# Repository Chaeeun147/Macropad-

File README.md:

This is my  number macropad called Bento Buttons!!

It has 9 buttons arranged in a standard 3-by-3 MX switch layout, with each button assigned a number. It also has custom keycaps I made.

I decided to make this because I saw my friend have one and thought it was very nice. But I never found a justifiable reason to buy it for myself. So I decided, instead of buying one with money, I should make it myself! Therefore, I made this project!

Case Onspae Project Link:
https://cad.onshape.com/documents/b9ad67c2619a28230095964c/w/e97b6c9aa4d60c46a3c97c60/e/4f1c892a648408b650cc743c?renderMode=0&uiState=69ecc582b69343973a4b0322

Keycap Onshape Project Link:
https://cad.onshape.com/documents/011ac684179c40686769cfd5/w/52282f15d2c1c6dc678585c8/e/da4142377097f970f64a90cc?renderMode=0&uiState=69ecc4f1b2576af614260f4a

3D Model:

PCB 3D Viewer:

PCB:

Schematic:

Case:

Keycaps:

BOM:
| Part Name | Quantity | Description | Cost | Link  |
| --------- | -------- | ----------- | ---- | - |
| Xiao RP 2040 | 1 | PCB | $3.59 |https://www.aliexpress.com/item/1005003908237026.html?spm=a2g0o.cart.0.0.6df938dabXCDew&mp=1&pdp_npi=6%40dis%21CAD%21CAD+11.73%21CAD+4.93%21%21CAD+4.75%21%21%21%40210328df17740487064442830e3672%2112000056511616306%21ct%21CA%217451194651%21%216%210%21) |
| Cherry MX Switch | 10 | Input | $2.60 | https://www.aliexpress.com/item/1005008811335051.html?spm=a2g0o.cart.0.0.6df938dabXCDew&mp=1&pdp_npi=6%40dis%21CAD%21CAD+52.73%21CAD+45.79%21%21CAD+44.15%21%21%21%40210328df17740487064442830e3672%2112000046764301536%21ct%21CA%217451194651%21%211%210%21 |
| Custom PCB | 5 | PCB | $2.00 | https://jlcpcb.com/ |
| 3D Printing | 1 | 3D Printing | $0.00 |  |

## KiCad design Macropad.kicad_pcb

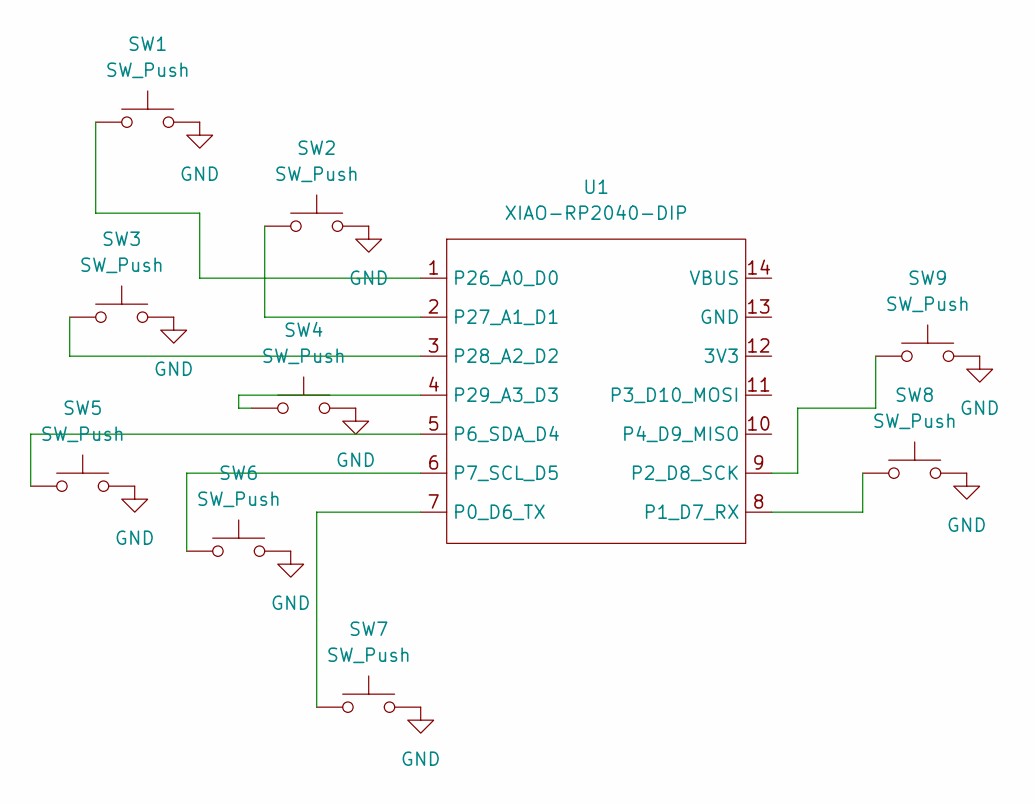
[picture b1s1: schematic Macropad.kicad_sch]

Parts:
SW1, SW2, SW3, SW4, SW5, SW6, SW7, SW8, SW9: SW_Push; SW_Cherry_MX_1.00u_PCB
U1: XIAO-RP2040-DIP

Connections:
GND: SW1.2, SW2.2, SW3.2, SW4.2, SW5.2, SW6.2, SW7.2, SW8.2, SW9.2
unnamed: SW7.1, U1.7 (P0_D6_TX)
unnamed: SW8.1, U1.8 (P1_D7_RX)
unnamed: SW9.1, U1.9 (P2_D8_SCK)
unnamed: SW5.1, U1.5 (P6_SDA_D4)
unnamed: SW6.1, U1.6 (P7_SCL_D5)
unnamed: SW1.1, U1.1 (P26_A0_D0)
unnamed: SW2.1, U1.2 (P27_A1_D1)
unnamed: SW3.1, U1.3 (P28_A2_D2)
unnamed: SW4.1, U1.4 (P29_A3_D3)

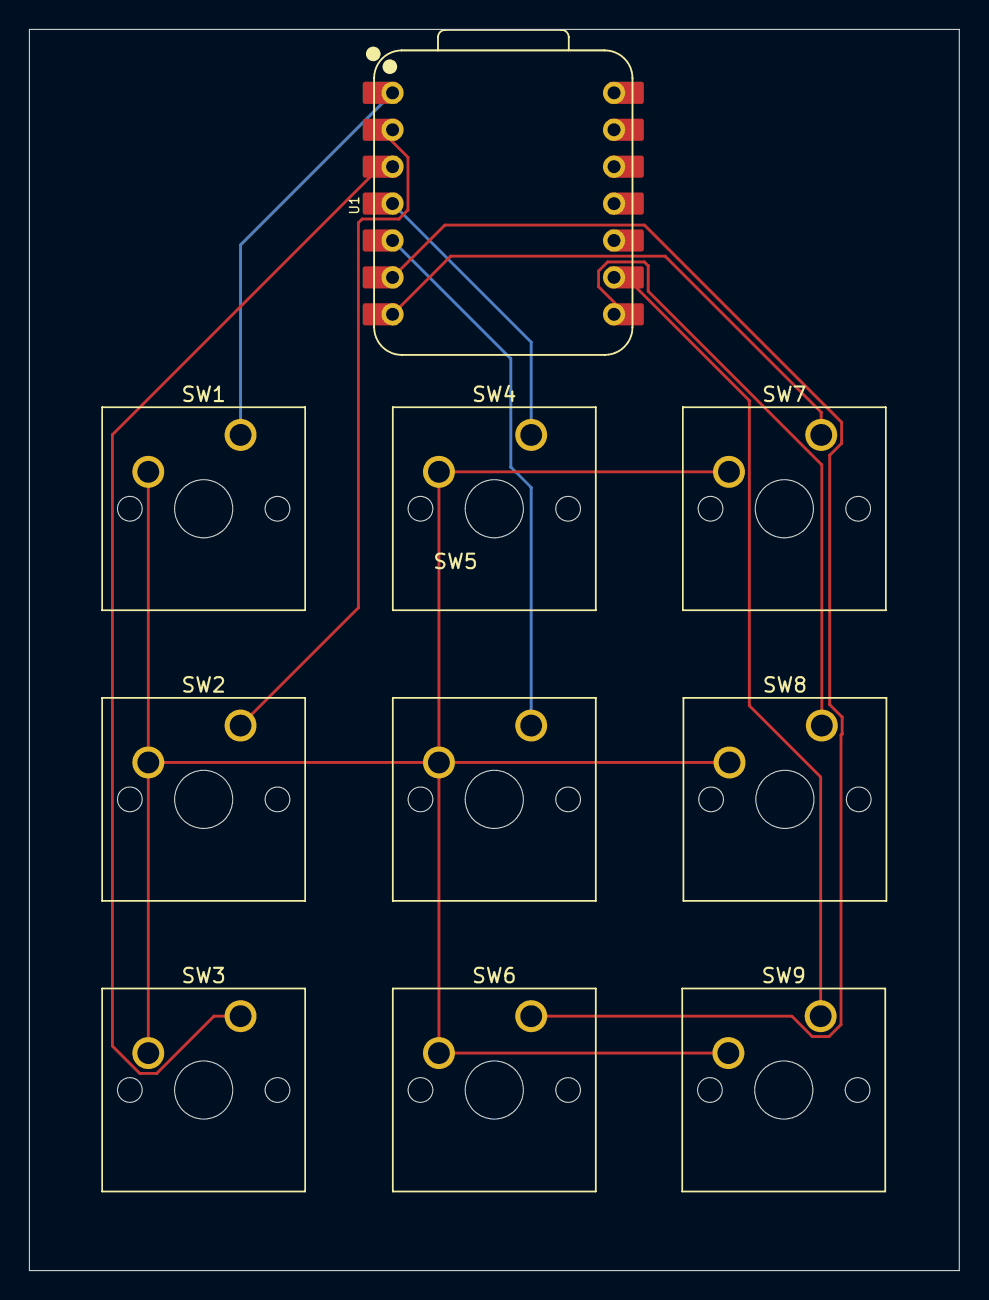
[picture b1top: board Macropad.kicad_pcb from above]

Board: 2 copper layers, 64.0 x 85.4 mm, 10 parts (0 on the bottom side), 10 nets.

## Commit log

2026-04-25 Update BOM with new parts and links
2026-04-25 Enhance README with project details and images
    Expanded the README with detailed project information, including layout, custom keycaps, and images of the 3D model, PCB, schematic, and BOM.
2026-04-25 Remove image tag from README
    Removed image tag from the README file.
2026-04-25 Update README with project introduction
    Added a brief introduction about the Bento Buttons macropad project.
2026-04-25 Update README with Onshape project links
    Added links to Onshape projects for case and keycap designs.
2026-04-25 Add Macropad case section to README
    Added a section for the Macropad case with an image.
2026-05-13 Add 3D Printing entry to the components table
2026-05-30 Create STL Files
